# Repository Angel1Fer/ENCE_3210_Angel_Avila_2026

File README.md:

# ENCE 3210 Microprocessors 1  
Here you will find all the work I have done during this course
## Coursework documentation  
There are 2 main files:  
Lab: 1, 2, 3   
Documentation_C  
(Note- Documentation_C contains Phase B as well)  
## Please select what you'd like to see

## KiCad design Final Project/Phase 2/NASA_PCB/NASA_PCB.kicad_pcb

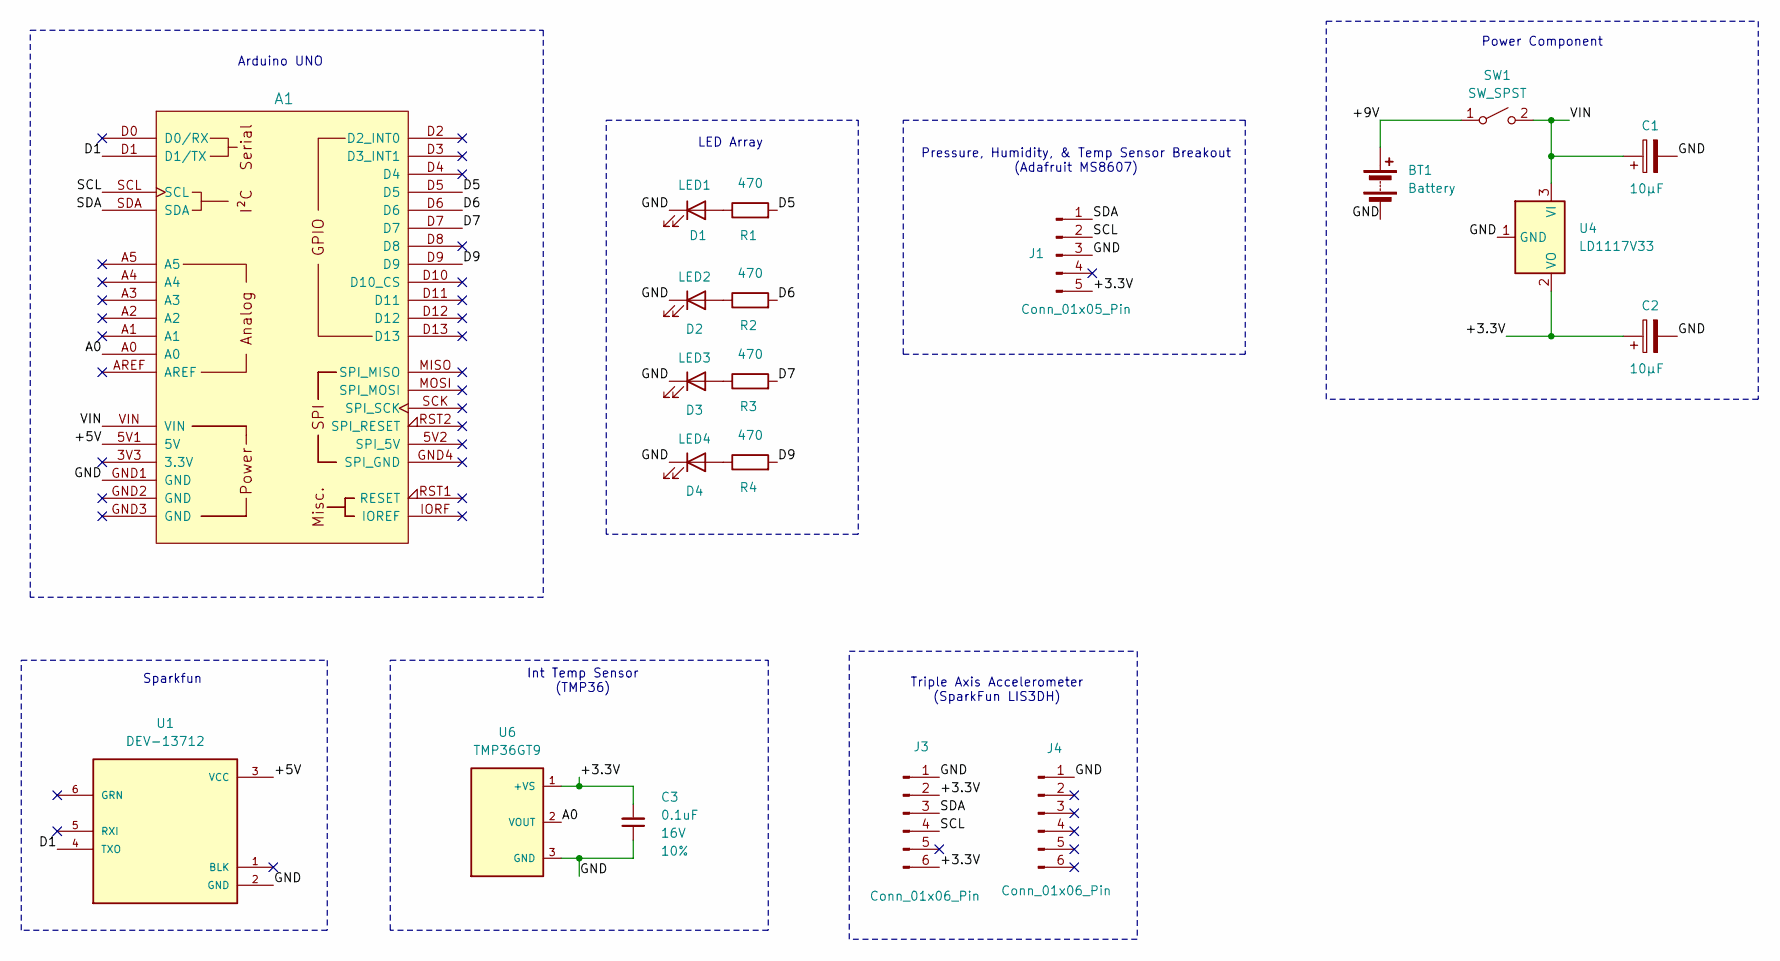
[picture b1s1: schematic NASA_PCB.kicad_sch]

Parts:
A1: Arduino_Uno_R3_Shield
BT1: Battery; PinHeader_1x02_P2.54mm_Vertical
C1, C2: 10µF; CP_Radial_D5.0mm_P2.00mm
C3: 0.1uF; C_Disc_D3.0mm_W1.6mm_P2.50mm; Voltage 16V; Tolerance 10%
D1: LED1; LED_D3.0mm
D2: LED2; LED_D3.0mm
D3: LED3; LED_D3.0mm
D4: LED4; LED_D3.0mm
J1: Conn_01x05_Pin; PinHeader_1x05_P2.54mm_Vertical
J3, J4: Conn_01x06_Pin; PinHeader_1x06_P2.54mm_Vertical
R1, R2, R3, R4: 470; R_Axial_DIN0207_L6.3mm_D2.5mm_P7.62mm_Horizontal
SW1: SW_SPST; PinHeader_1x02_P2.54mm_Vertical
U1: DEV-13712; MODULE_DEV-13712; PARTREV v15
U4: LD1117V33; TO-220-3_Vertical
U6: TMP36GT9; XDCR_TMP36GT9; PARTREV H

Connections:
/+3.3V: C2.1, C3.2, J1.5, J3.2, J3.6, U4.2 (VO), U6.1 (+VS)
/+5V: A1.5V1 (5V), U1.3 (VCC)
/+9V: BT1.1 (+), SW1.1 (A)
/A0: A1.A0, U6.2 (VOUT)
/D1: A1.D1 (D1/TX), U1.4 (TXO)
/D5: A1.D5, R1.2
/D6: A1.D6, R2.2
/D7: A1.D7, R3.2
/D9: A1.D9, R4.2
/GND: A1.GND1 (GND), BT1.2 (-), C1.2, C2.2, C3.1, D1.1 (K), D2.1 (K), D3.1 (K), D4.1 (K), J1.3, J3.1, J4.1, U1.2 (GND), U4.1 (GND), U6.3 (GND)
/SCL: A1.SCL, J1.2, J3.4
/SDA: A1.SDA, J1.1, J3.3
/VIN: A1.VIN, C1.1, SW1.2 (B), U4.3 (VI)
unnamed: D1.2 (A), R1.1
unnamed: D2.2 (A), R2.1
unnamed: D3.2 (A), R3.1
unnamed: D4.2 (A), R4.1

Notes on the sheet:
Triple Axis Accelerometer (SparkFun LIS3DH)
LED Array
Arduino UNO
Power Component
Sparkfun
Int Temp Sensor (TMP36)
Pressure, Humidity, & Temp Sensor Breakout (Adafruit MS8607)

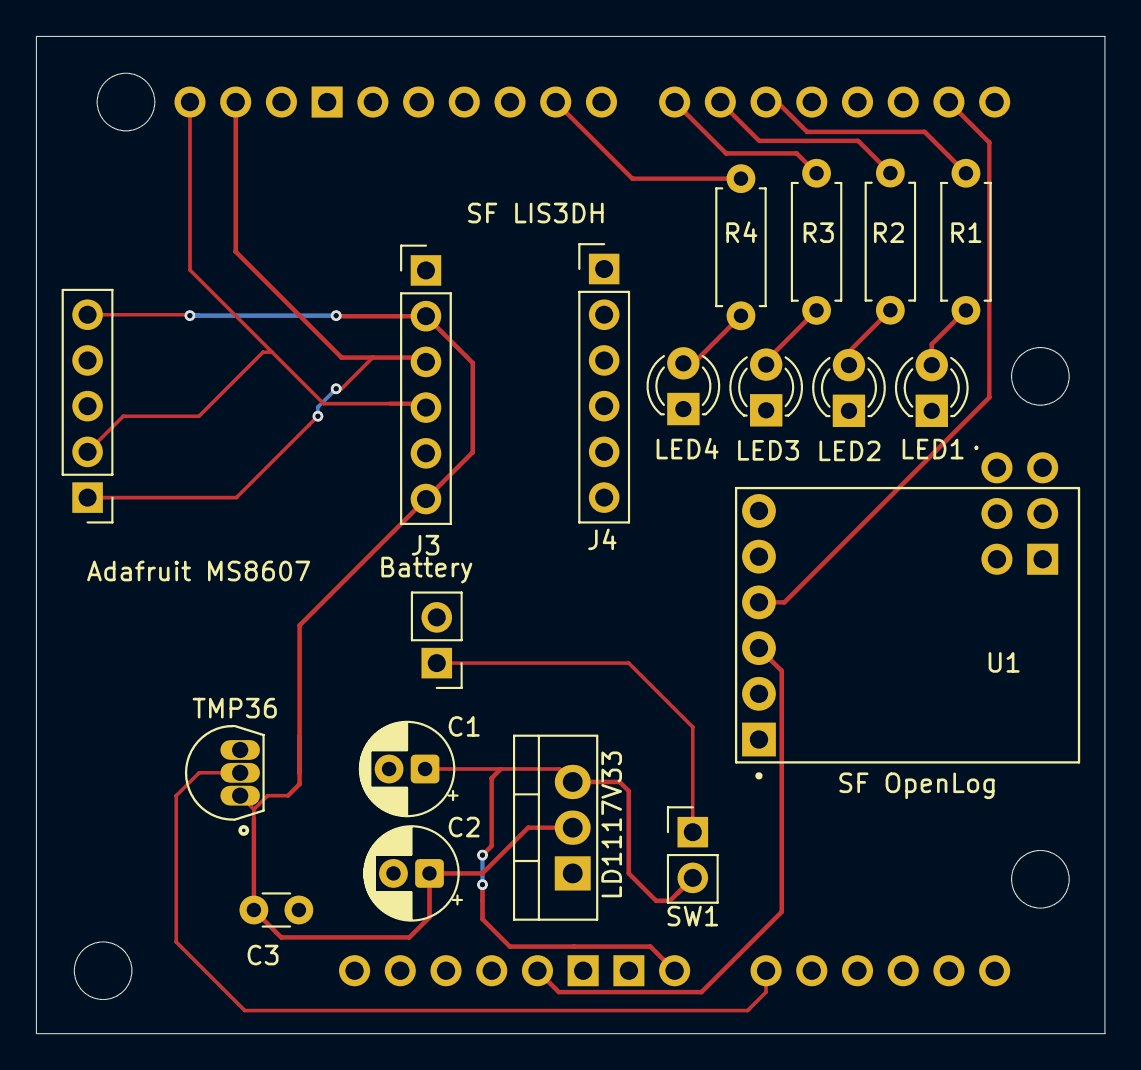
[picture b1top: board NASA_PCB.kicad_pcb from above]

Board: 2 copper layers, 59.4 x 55.4 mm, 20 parts (0 on the bottom side), 17 nets.

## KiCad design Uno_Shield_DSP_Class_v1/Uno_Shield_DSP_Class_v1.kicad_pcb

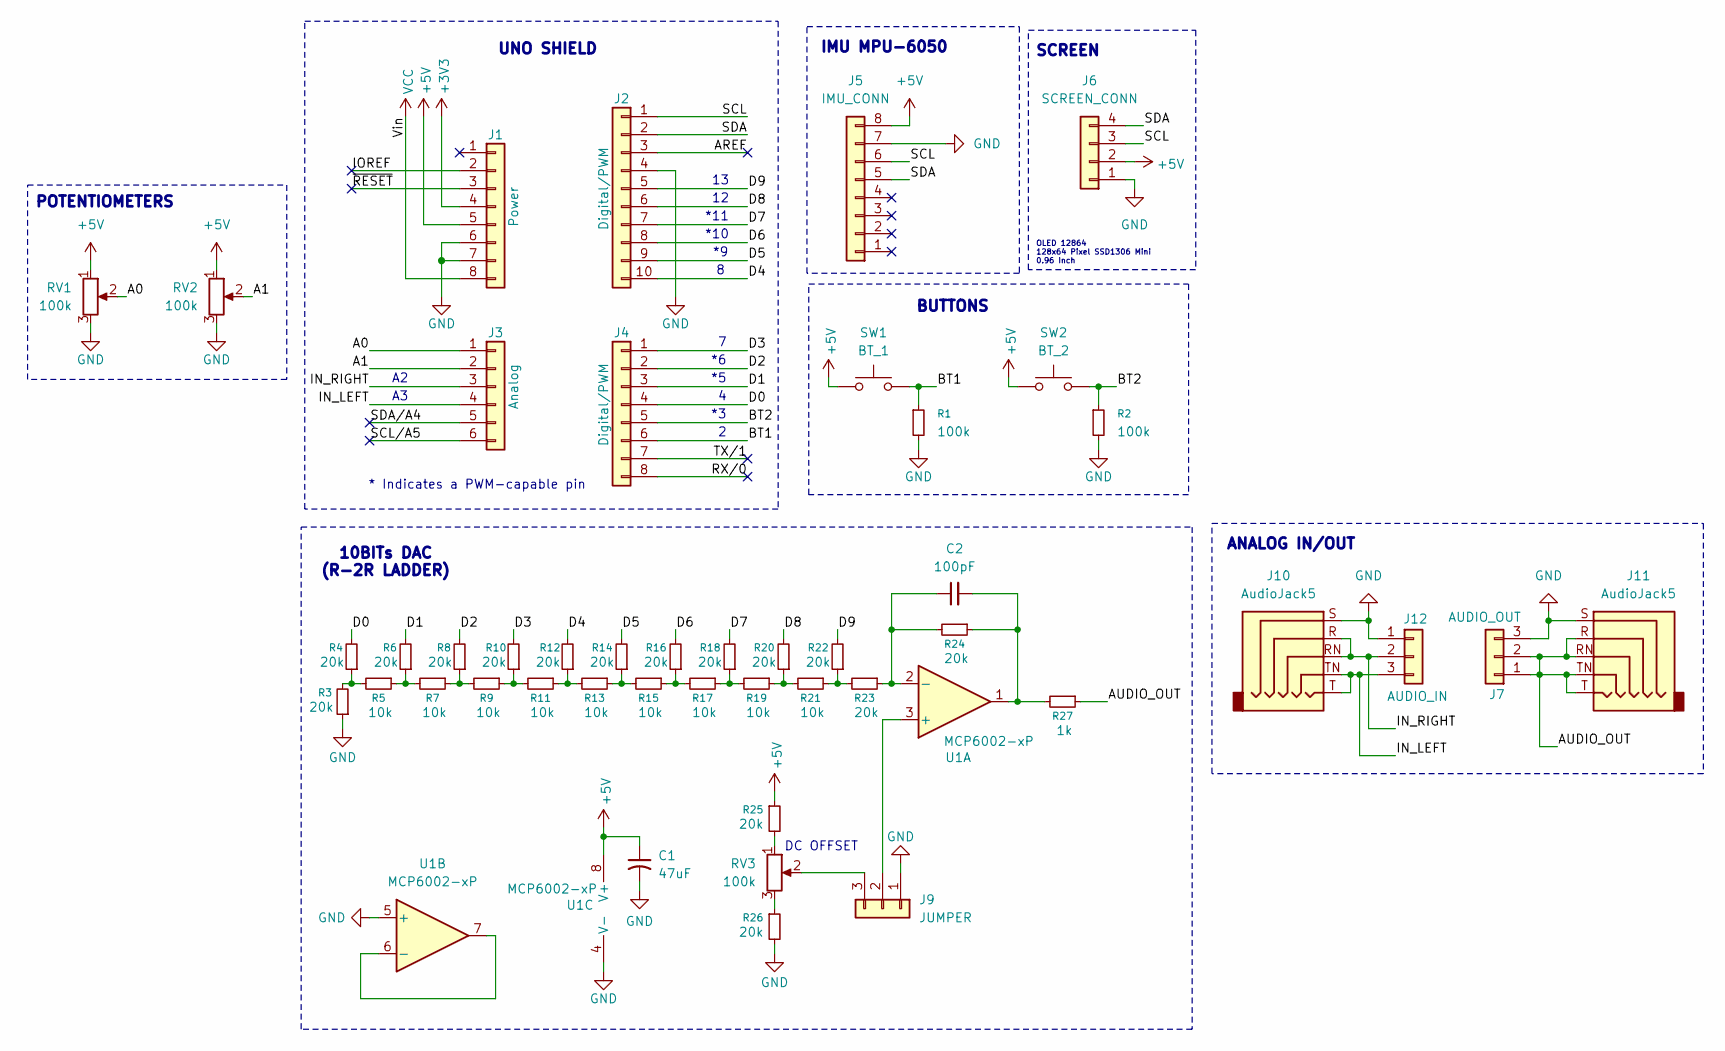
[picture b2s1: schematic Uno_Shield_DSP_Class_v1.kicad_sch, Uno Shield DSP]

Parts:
C1: 47uF; CP_Radial_D8.0mm_P2.50mm
C2: 100pF; C_Disc_D5.0mm_W2.5mm_P2.50mm
J1: Power; PinSocket_1x08_P2.54mm_Vertical
J2: Digital/PWM; PinSocket_1x10_P2.54mm_Vertical
J3: Analog; PinSocket_1x06_P2.54mm_Vertical
J4: Digital/PWM; PinSocket_1x08_P2.54mm_Vertical
J5: IMU_CONN; PinSocket_1x08_P2.54mm_Vertical
J6: SCREEN_CONN; PinHeader_1x04_P2.54mm_Vertical
J7: AUDIO_OUT; PinHeader_1x03_P2.54mm_Vertical
J9: JUMPER; PinHeader_1x03_P2.54mm_Vertical
J10, J11: AudioJack5; Jack_3.5mm_CUI_SJ1-3525N_Horizontal
J12: AUDIO_IN; PinHeader_1x03_P2.54mm_Vertical
R1, R2: 100k; R_Axial_DIN0309_L9.0mm_D3.2mm_P2.54mm_Vertical
R3, R4, R6, R8, R10, R12, R14, R16, R18, R20, R22, R23, R24, R25, R26: 20k; R_Axial_DIN0309_L9.0mm_D3.2mm_P2.54mm_Vertical
R5, R7, R9, R11, R13, R15, R17, R19, R21: 10k; R_Axial_DIN0309_L9.0mm_D3.2mm_P2.54mm_Vertical
R27: 1k; R_Axial_DIN0309_L9.0mm_D3.2mm_P2.54mm_Vertical
RV1, RV2, RV3: 100k; Potentiometer_Bourns_3386P_Vertical
SW1: BT_1; SW_PUSH_6mm
SW2: BT_2; SW_PUSH_6mm
U1: MCP6002-xP; DIP-8_W7.62mm_Socket_LongPads

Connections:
+3V3: J1.4
+5V: C1.1, J1.5, J5.8, J6.2, R25.1, RV1.1, RV2.1, SW1.1, SW2.1, U1.8 (V+)
/A0: J3.1, RV1.2
/A1: J3.2, RV2.2
/AREF: J2.3
/AUDIO_OUT: J7.1, J7.2, J11.R, J11.RN, J11.T, J11.TN, R27.1
/BT1: J4.6, R1.1, SW1.2
/BT2: J4.5, R2.1, SW2.2
/D0: J4.4, R4.2
/D1: J4.3, R6.2
/D2: J4.2, R8.2
/D3: J4.1, R10.2
/D4: J2.10, R12.2
/D5: J2.9, R14.2
/D6: J2.8, R16.2
/D7: J2.7, R18.2
/D8: J2.6, R20.2
/D9: J2.5, R22.2
/IN_LEFT: J3.4, J10.T, J10.TN, J12.3
/IN_RIGHT: J3.3, J10.R, J10.RN, J12.2
/IOREF: J1.2
/RX/0: J4.8
/SCL: J2.1, J5.6, J6.3
/SCL/A5: J3.6
/SDA: J2.2, J5.5, J6.4
/SDA/A4: J3.5
/TX/1: J4.7
/~RESET: J1.3
GND: C1.2, J1.6, J1.7, J2.4, J5.7, J6.1, J7.3, J9.1, J10.S, J11.S, J12.1, R1.2, R2.2, R3.1, R26.2, RV1.3, RV2.3, U1.4 (V-), U1.5 (+)
unnamed: C2.2, R24.1, R27.2, U1.1
unnamed: J9.2, U1.3 (+)
unnamed: J9.3, RV3.2
unnamed: R3.2, R4.1, R5.2
unnamed: R5.1, R6.1, R7.2
unnamed: R7.1, R8.1, R9.2
unnamed: R9.1, R10.1, R11.2
unnamed: R11.1, R12.1, R13.2
unnamed: R13.1, R14.1, R15.2
unnamed: R15.1, R16.1, R17.2
unnamed: R17.1, R18.1, R19.2
unnamed: R19.1, R20.1, R21.2
unnamed: R21.1, R22.1, R23.2
unnamed: R25.2, RV3.1
unnamed: R26.1, RV3.3
unnamed: C2.1, R23.1, R24.2, U1.2 (-)
unnamed: U1.6 (-), U1.7
VCC: J1.8

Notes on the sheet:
BUTTONS
IMU MPU-6050
POTENTIOMETERS
*11
DC OFFSET
10BITs DAC (R-2R LADDER)
ANALOG IN/OUT
*10
OLED 12864 128x64 Pixel SSD1306 Mini 0.96 Inch
* Indicates a PWM-capable pin
SCREEN
UNO SHIELD

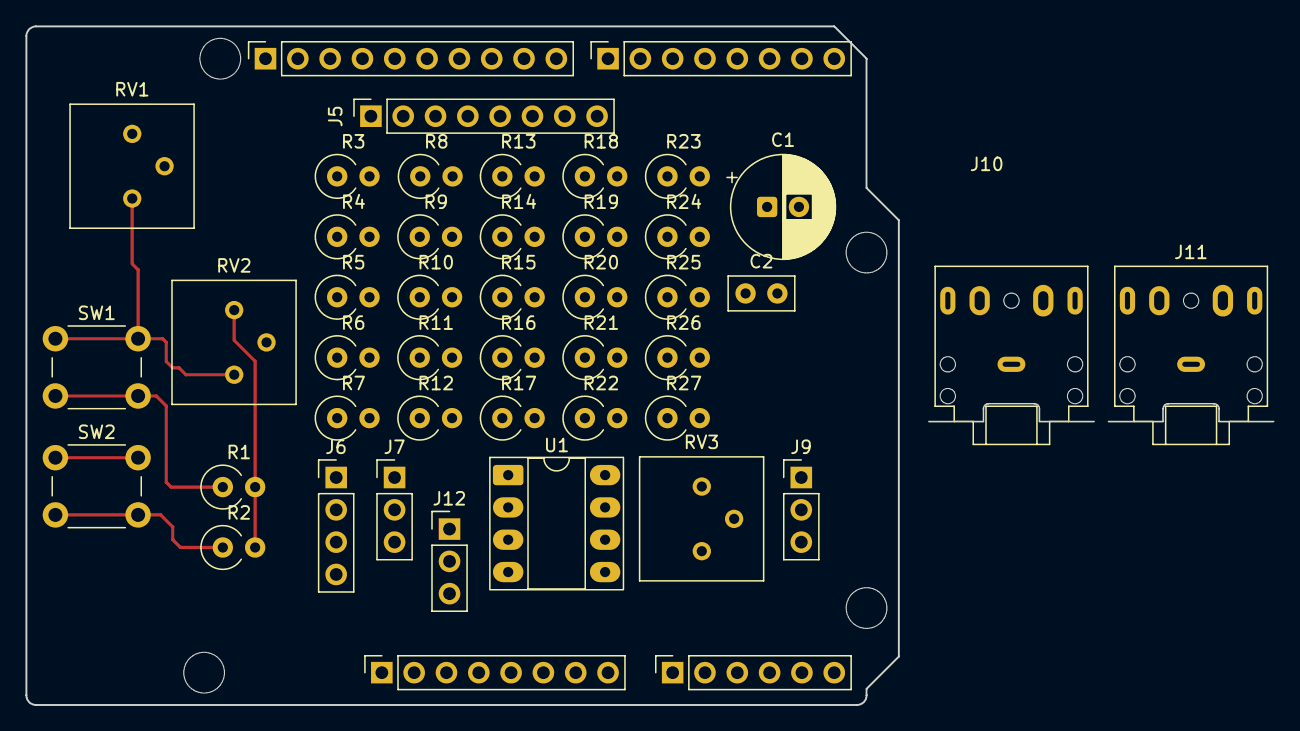
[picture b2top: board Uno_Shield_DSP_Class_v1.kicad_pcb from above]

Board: 2 copper layers, 68.6 x 53.3 mm, 50 parts (0 on the bottom side), 38 nets.

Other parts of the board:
MH1, MH2, MH3, MH4: MountingHole_3.2mm

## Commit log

2026-01-09 Create README.md
    Lab 1 folder
2026-01-26 Create Lab2_Question1_3210.ino
    made lab 2 folder, added Q1
2026-01-27 Create Lab2_Question_4_3210.ino
    added Q4
2026-01-27 Question #5
2026-01-27 Questions 6 & 7 completed
2026-02-04 PCB zipfile
2026-02-04 Project file
2026-02-04 try again
2026-02-09 All task should be working, test on Arduino
2026-02-09 Block diagram upload
2026-02-16 PCB_upload 1st test
2026-02-16 fixing gerber
2026-02-16 Images
2026-03-09 Clean up Main
2026-03-09 Doc_C condensing
2026-03-09 fix 1
2026-03-09 text?
2026-03-09 no worries
2026-03-09 Introduction
2026-03-09 Design Phase
2026-03-09 Design Info
2026-03-09 Phase B
2026-03-09 DSP Assembled
2026-03-09 Assembly Info
2026-03-09 Assembly Phase
2026-03-09 Test Phase
2026-03-09 Final Project Phase 1
2026-03-09 Phase_1
2026-03-09 Phase1 Discription
2026-03-13 upload gerber
2026-03-13 edits
2026-03-13 should work now
2026-03-13 final presentation
